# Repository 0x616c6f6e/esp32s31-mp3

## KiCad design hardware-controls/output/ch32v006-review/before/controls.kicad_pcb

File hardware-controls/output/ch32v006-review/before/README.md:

# 滑环与按键小板 B：I²C 四键＋独立 POWER

## 当前生产版本：2026-09-22，无测试点

已同步移除原理图和 PCB 中 TP1～TP11，清理 70 段分支走线及 5 个冗余过孔。当前为 31 个封装对象（26 个装配元件、1 个触摸电极、4 个安装孔）、442 段走线、52 个过孔。其余封装位置、接口针序和功能网络保持不变；ERC、DRC、未连接项和原理图一致性问题均为 0。

最新生产包：[controls-jlcpcb-20260922-no-tp-gerbers.zip](output/controls-jlcpcb-20260922-no-tp-gerbers.zip)。双层 FR-4、44 × 34 mm、0.8 mm 板厚，52 个 Ø0.30 mm 镀铜过孔、4 个 Ø1.80 mm 非金属化安装孔。请使用此包，旧带测试点版仅保留作历史记录。最新 BOM 为 [controls-jlcpcb-20260922-bom.csv](output/controls-jlcpcb-20260922-bom.csv)，10 类、单板 26 个元件，LCSC 料号尚待匹配。

检查报告、前后对比图及修改前备份位于 [output/remove-testpoints](output/remove-testpoints/README.md)。旧 STEP / FreeCAD 装配未重新导出。

## 2026-09-22 GND 铺铜优化

当前 `controls.kicad_pcb` 已增加双面 GND 铺铜，GND 走线从 99 段减至 75 段（减少约 26.59 mm），保留 12 个必要的 GND 过孔。E1 触摸电极及其背面设置禁铺铜区，轮廓外扩约 0.8 mm；三路 WHEEL/SENSE 走线按铜边再外扩约 0.5 mm 避让。这些是本版设计余量，触摸灵敏度仍需结合覆盖层实测调参。

铺铜间距 0.20 mm、最小铜宽 0.25 mm、热焊盘间隙/辐条宽 0.20 mm，移除孤立铜岛。所有封装定义、元件位置、原理图、信号走线和板框均保持不变。KiCad 10.0.4 原生重铺铜后的 DRC 为 0 违规、0 未连接、0 原理图一致性问题。

此次铺铜阶段报告、前后对比图及备份位于 [output/ground-plane-review](output/ground-plane-review/README.md)。对应的 `controls-jlcpcb-20260922-gerbers.zip` 带有测试点，已被上面的无测试点版替代。下文旧 `fabrication/`、Gerber ZIP 以及历史 STEP 和 validation/fit 报告均为历史版本。

打开 **controls.kicad_pro**。这是独立工程，已按用户完成布局的 `hardware-q2-layout` 主板设计 FFC 对接，主板文件未修改；原理图与 PCB 的符号路径和网络已对应。配套装配为 `mechanical/Q2_Controls_Assembly.FCStd`。

## 电路与布局

- 44 × 34 × 0.8 mm、R10、双层板；沿用 F 版外壳的四个 Ø1.8 安装孔和五个按键中心。
- 正面 E1 为三个相互插值的电容触摸电极，外径 31 mm、内径 15 mm，留出四个开关窗口。电极覆盖阻焊，无锡膏；不使用旧机械模型里的十二个示意扇区。
- U1：AT42QT2120-MMHR，3.3 V，I²C 地址 0x1C。三路 10 kΩ 采样串阻、22 Ω 电源滤波、100 nF / 1 µF 去耦；SDA/SCL 各 4.7 kΩ 上拉，共享 INT_N / RESET_N 各 10 kΩ 上拉。
- U2：TCA6408ARGTR，RGT VQFN-16，3 × 3 mm，0.5 mm 脚距，最大高 1 mm。ADDR 接地，7 位地址 0x20；VCCI、VCCP 共用 +3V3，各有 100 nF 去耦。散热焊盘接地。封装焊盘和本地包络模型依据 TI RGT0016A 图。
- 五个 ALPS SKSWCEE010，3 × 2 mm、标称高 0.6 ±0.05 mm、1.8 N、行程 0.13 mm。BACK / PREV / NEXT / PLAY 分别接 U2 P0 / P1 / P2 / P3，R9…R12 各 47 kΩ 上拉，按下为低；只通过 I²C 向外部主机报告这四键。
- POWER 独立引出：SW1.1 → J1.11，R14 = 10 kΩ 上拉至小板 +3V3；上电后松开为高、按下接地为低。不接 U1/U2，按下时上拉支路电流约 0.33 mA。高电平依赖小板供电，本版未实现整机开关机；若需要关机唤醒，须在主板设计中确认上拉电源为常供电域。
- U2 未用的 P4…P7 共接 UNUSED_INPUTS，由 R13 = 10 kΩ 下拉，避免上电浮空。这四脚必须一直配置为输入；不要用作输出或连接外设。
- U1 CHANGE 和 U2 INT 均为开漏输出，共接 INT_N；RESET_N 也由两芯片共用。主控轮询仅需 SDA/SCL，有中断通知时合计 3 个 IO；RESET_N 是可选调试/恢复信号，不接时由上拉保持高。
- 芯片及无源件在背面、避开电池和马达占位。新增 U2 与无源件布置在电池下方区域，正面五键及板框不变。J1 改为与主板 FPC1 相同的 HC-FPC-05-10-12RLTAG，12 芯、0.5 mm 间距、下接点，适配 0.30 ±0.03 mm 端部厚度。KiCad 坐标 (8.130, 9.411) mm、B.Cu、−90°；它不是屏幕接口。
- 已完成新主板 FPC1 与小板 J1 的针序对照和 40 mm 成品 FFC 名义装配路线；详见 [FFC 对接与采购说明](mechanical/FFC-INTERCONNECT.md)。整机开关机逻辑与实物连接尚未验证。

## J1 引脚

按 **焊盘编号** 接线，不能根据排线同面／反面的外观直接推断另一端编号。

| 引脚 | 信号 | 用途 |
|---|---|---|
| 1 | GND | 地 |
| 2 | +3V3 | 稳压 3.3 V 输入 |
| 3 | SDA | I²C 数据 |
| 4 | SCL | I²C 时钟 |
| 5 | INT_N | 滑环＋四键共享低有效开漏中断 |
| 6 | RESET_N | 两芯片共享低有效复位；可不接 |
| 7…10 | NC | 不连接；不再引出四个普通按键 |
| 11 | KEY_POWER | 独立电源键，10 kΩ 上拉；按下为低 |
| 12 | GND | 地 |
| 13、14 | GND | 金属固定脚，不计入 12 芯排线 |

TP1～TP11 已移除。调试电源、I²C、中断、复位和 POWER 可从 J1 对应引脚测量，四个机械键输入可从 U2 或开关焊盘测量。

## 独立上电与调试

1. 用限流的稳压 3.3 V 给 J1.2/J1.1 供电。不得输入电池原始电压。主机逻辑电平也使用 3.3 V。
2. 先以 100 kHz I²C 访问 7 位地址 0x1C，读寄存器 0x00，预期芯片 ID 为 0x3E。
3. 寄存器 0x0E 写 0xC0，启用 KEY0…KEY2 的环形模式；KEY0…KEY2 的控制寄存器保持触摸输入配置。
4. 未使用的 KEY3…KEY11 不应浮空扫描：对应十进制地址 31…39 的控制寄存器写 0x01，配置为输出低电平，焊盘不接外部网络。配置后按数据手册执行重新校准，并等待校准完成。
5. 读取检测状态和滑环位置，检查一整圈的连续性、零点回绕、方向及按压时的误触。阈值、脉冲数、积分、低功耗周期须结合成品覆盖层实测设定；本项目没有凭空填入“已验证”的灵敏度参数。
6. 初始化 U2，访问 7 位地址 0x20：先向输出寄存器 0x01 写 0x00（设安全的输出锁存值，不改变方向），向极性寄存器 0x02 写 0x00，向方向寄存器 0x03 写 0xFF，保持所有端口为输入。读回 0x02 / 0x03 核对配置。不要把共接的 P4…P7 配成输出。
7. 读取 U2 输入寄存器 0x00。正常未按时低四位为 0x0F，高四位为 0；`pressed = (~input) & 0x0F`。bit0=BACK，bit1=PREV，bit2=NEXT，bit3=PLAY，可识别同时按下。建议每 5 ms 采样并连续稳定 20 ms 后确认变化；长按/连击由主控处理。
8. INT_N 触发时，分别读取 U1 的状态字节和 U2 的输入寄存器，清除两边的中断来源；只读取其中一颗可能让中断一直为低。初始化后主动读一次两颗芯片，正常服务中应持续处理到 INT_N 释放，并设置有界重试、周期补读及总线错误恢复，不能仅等待下一个下降沿。即使中断已释放，也继续定时采样直到机械键消抖完成；U2 不会为静止的按键反复触发中断。
9. 小板上电后测试 POWER：J1.11 松开时约 3.3 V，按下时约 0 V；确认不影响 U2 低四位。R14 已提供上拉，主机端按 3.3 V 逻辑输入读取并进行消抖。未来接入整机电源管理时确认其电源域和关机唤醒要求。

若测试主机已有 I²C 上拉，应计算并联后的总阻值，必要时不装 R4/R5。RESET_N 未连接时由 R7 保持高电平；外部拉低至少 10 ms 并释放后须重新初始化两颗 IC，等待触摸校准完成。J1 输入电源应与主机 I²C 电平同步，不能在小板断电时持续用信号线反向供电。小板掉电重启后也必须重新初始化。

## 外壳适配

`mechanical/` 单独保存适配版本，没有覆盖 F 版外壳源文件。

- 保持整机外观、按键中心、板框和安装高度。小板下表面 Z=11.1、上表面 Z=11.9 mm。
- 修正原键帽的内部压柱、限位环和壳体内部环槽；旧键帽直接套用会在开关触发前碰到 PCB。
- 新压柱底面 Z=12.65 mm。考虑开关高度公差，静态间隙为 0.10…0.20 mm；名义触发行程 0.28 mm，按高度下限计算为 0.33 mm。
- `fit-check.json` 检查小板和 26 个元件、电池／移位后的马达／新主板已建模元件与外壳的名义实体相交（不包含未重布的电池和马达线束），检查 0.33 mm 轴向下压，以及四个方向的约 ±0.727° 倾斜加 0.165 mm 下移姿态。U2 包络使用最大 1 mm 高度；其他尺寸仍为名义尺寸。这些姿态只证明有可用运动空间，不等同于受力、回弹、摇摆手感或寿命验证，需打印实物确认。
- 电池仍为 24 × 34 × 3 mm 占位，板底到电池名义间隙仅 0.3 mm；实际电池厚度、膨胀余量及绝缘层需要重新核对，不能据此选用更厚电池。
- 滑环上方存在约 1.05 mm 空气间隙及 0.6 mm 键帽。键帽使用非导电塑料，不做导电镀层。空气间隙与按压运动会影响触摸，需要整机调试；本版是待验证的原型设计。

FreeCAD 文件包含可重算的内部圆柱、切除与融合特征；`HousingControlsA`、`WheelControlsA`、`CenterButtonControlsA` 分别提供 STEP / STL，后盖增加局部内部 FFC 避让槽并导出 `RearCoverWithPCBPosts.step/.stl`，外表面保持不变。马达中心从壳体 (39, 57) 移到 (39, 62) mm，电池不变；U1 向壳体 +X 平移 0.6 mm 以避让新主板耳机座。新主板 1.6 mm 厚；2026-09-22 完整复查确认最终主板四个安装孔与原固定柱对齐；同时发现马达/耳机座及 C13/屏幕排线干涉，不能将旧的局部通过报告视为整机装配通过。最新装配与报告见 `../mechanical/final-board-review/`。打开装配默认显示外观，可展开 `ControlsPCB`、`References` 查看内部。

## 文件与检查

- `controls.kicad_sch` / `controls.kicad_pcb`：实际独立小板设计；本地 `Controls.pretty`、`Controls.kicad_sym`、`models3d` 随工程携带。
- `output/bom.csv`：26 个装配元件的型号与数据手册。
- `output/erc.json`、`output/drc.json`、`output/validation.json`：最终原生 KiCad 检查与保存文件的校验摘要。
- `fabrication/`：双面 Gerber、钢网层及分开的 PTH / NPTH 钻孔；`output/controls-B-prototype-gerbers.zip` 为 B 版原型打样包。制造参数见包内说明。
- `output/schematic.png` / `output/schematic/controls.svg`：可直接查看的原理图。
- `output/controls-populated.step`：小板 STEP；FreeCAD 检查将 KiCad 导出的介质厚度扩展为 0.8 mm 成品板包络。
- `mechanical/fit-check.json`：名义装配与轴向行程检查，包含源文件校验值。

本版尚未经过实物焊接、触摸调参、ESD、按键寿命或整机验证。DRC/ERC 与名义几何通过只证明相应的设计规则和包络检查通过。

## 设计依据与重建

原厂资料保存在 `reference/`，来源：[Microchip AT42QT2120](https://ww1.microchip.com/downloads/en/devicedoc/doc9634.pdf)、[Microchip QTAN0079](https://ww1.microchip.com/downloads/aemDocuments/documents/OTH/ApplicationNotes/ApplicationNotes/doc10752.pdf)、[ALPS SKSW](https://tech.alpsalpine.com/cms.media/product_catalog_ta_02_sksw_en_ee3e98d509.pdf)、[Hirose FH19C](https://www.hirose.com/en/product/p/CL0580-0413-0-10)。电极窗口和形状是本项目的实现，并非厂家验证过的参考 PCB。

B 版新增 [TI TCA6408A 数据手册](https://www.ti.com/lit/ds/symlink/tca6408a.pdf)：§5 核对 RGT 引脚；§8.3.3 开漏中断；§8.6 寄存器/0x20 地址；RGT0016A 图核对 3 × 3 mm / EP 1.45 × 1.45 mm 封装。A 版机械零件内部名称 `HousingControlsA` 等保留，保留历史名称；本次新增后盖内部排线避让，不改变外观和按键中心。

`make_electrodes.py` 需要 Python + Shapely；`build_design.py`、`finalize_board.py`、`validate.py` 使用 KiCad 10 的 Python/pcbnew；`build_models.py`、`build_fit.py` 使用 FreeCAD 1.1。生成脚本是本版设计记录，不应在手工修改后直接重跑覆盖。`build_design.py` 只生成初始原理图和摆放，会拒绝覆盖已有走线的板，不会重建最终布线。最终布线直接保存在 PCB；对应交换记录及说明在 `reference/routing/`。原生 KiCad DRC、连通性和原理图一致性是交付检查依据。

本次连接器依据 [HCTL HC-FPC-05-10 原厂图纸](https://atta.szlcsc.com/upload/public/pdf/source/20221027/B2DE489DA152049D1F105170189CFB4E.pdf)，本地副本为 `reference/HCTL-HC-FPC-05-10.pdf`。旧 Hirose 资料仅保留为历史参考，不能按其 0.2 mm 排线规格采购新 J1 的排线。

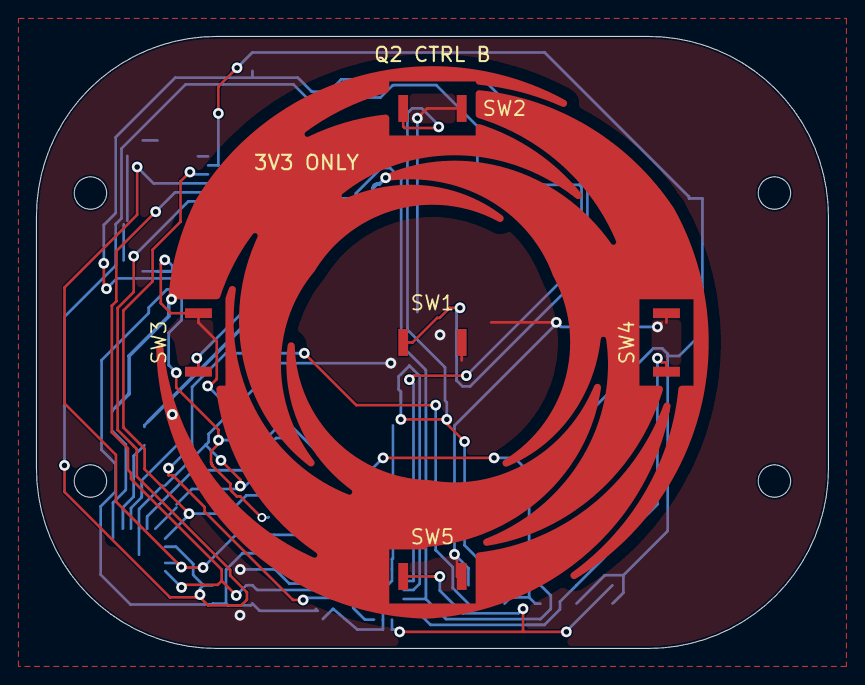
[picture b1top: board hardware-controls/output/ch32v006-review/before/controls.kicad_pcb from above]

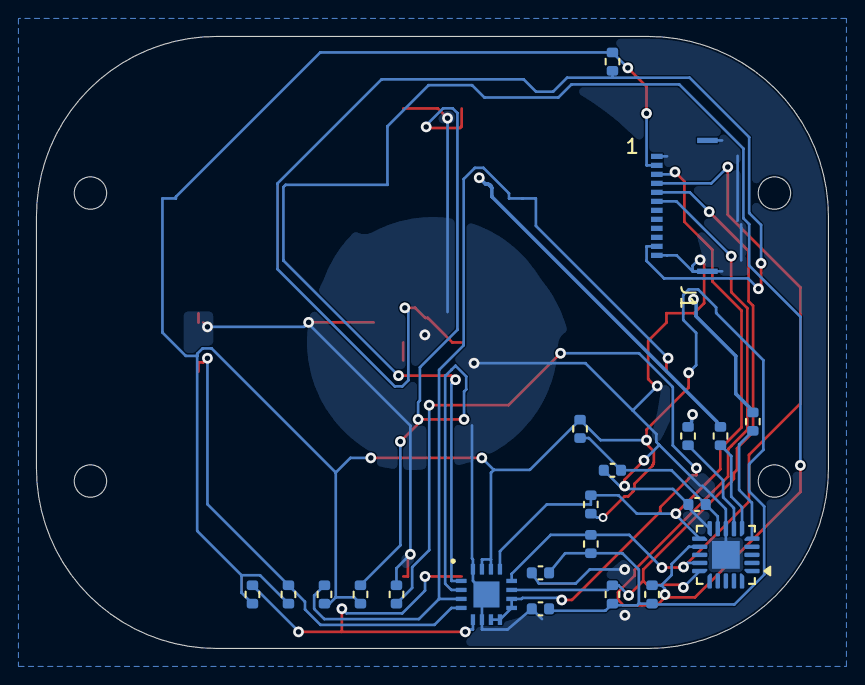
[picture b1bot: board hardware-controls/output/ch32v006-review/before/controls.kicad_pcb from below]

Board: 2 copper layers, 44.0 x 34.0 mm, 31 parts (21 on the bottom side), 19 nets.

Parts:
C1, C3, C4: 100nF; C0402
C2: 1uF; C0402
E1: 31mm INTERPOLATED WHEEL; Wheel_D31
H1, H2, H3, H4: M1.6 / NPTH 1.8; Mount_1.8
J1: HC-FPC-05-10-12RLTAG; HCTL_FPC12
R1, R2, R3, R6, R7, R13, R14: 10k; R0402
R4, R5: 4.7k; R0402
R8: 22R; R0402
R9, R10, R11, R12: 47k; R0402
SW1, SW2, SW3, SW4, SW5: SKSWCEE010; SKSW_3x2
U1: AT42QT2120-MMHR; QT2120_VQFN20
U2: TCA6408ARGTR; TCA6408A_VQFN16

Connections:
/+3V3: C3.1, C4.1, J1.2, R4.1, R5.1, R6.1, R7.1, R8.1, R9.1, R10.1, R11.1, R12.1, R14.1, U2.14, U2.15
/GND: C1.2, C2.2, C3.2, C4.2, J1.1, J1.12, J1.13, J1.14, R13.2, SW1.2, SW2.2, SW3.2, SW4.2, SW5.2, U1.8, U1.10, U1.21, U2.6, U2.16, U2.17
/INT_N: J1.5, R6.2, U1.15, U2.11
/KEY_BACK: R9.2, SW2.1, U2.2
/KEY_NEXT: R11.2, SW4.1, U2.4
/KEY_PLAY: R12.2, SW5.1, U2.5
/KEY_POWER: J1.11, R14.2, SW1.1
/KEY_PREV: R10.2, SW3.1, U2.3
/RESET_N: J1.6, R7.2, U1.12, U2.1
/SCL: J1.4, R5.2, U1.14, U2.12
/SDA: J1.3, R4.2, U1.11, U2.13
/SENSE0: R1.2, U1.7
/SENSE1: R2.2, U1.6
/SENSE2: R3.2, U1.5
/UNUSED_INPUTS: R13.1, U2.7, U2.8, U2.9, U2.10
/VDD_TOUCH: C1.1, C2.1, R8.2, U1.9
/WHEEL0: E1.1, R1.1
/WHEEL1: E1.2, R2.1
/WHEEL2: E1.3, R3.1

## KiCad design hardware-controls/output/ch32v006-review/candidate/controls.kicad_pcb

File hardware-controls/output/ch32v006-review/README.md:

# CH32V006 C 版迁移检查

源电路为 AT42QT2120 + TCA6408A；目标为单颗 CH32V006F8U6。`before/` 是本次操作前的原文件备份；`candidate/` 是工作候选文件。以 hardware-controls 根目录中的最终工程为准，不要从这里的中间 PCB 导出生产文件。

`design.json` 记录本版原理图 UUID、元件、实际 KiCad 顶视坐标、MCU 引脚与 FPC 接口。这里的坐标是实际 PCB 坐标，不能直接交给历史脚本中采用 `44-x` 镜像约定的机械生成器。

检查报告以 `final-erc.json`、`final-drc.json`、`validation.json` 为准；带 pre-route / routed / fanout / grid 字样的文件仅用于迁移过程诊断。模型预览用于检查元件体积与布局，不代替整机 FreeCAD 装配的干涉验证。

C 版需要新固件，详见 `../../CH32V006-interface.md`。本次没有生成可直接烧录的固件；旧 AT42 版本的 Gerber 和 BOM 不适用于 C 版。后续已于 2026-09-22 导出新版生产包 `../controls-ch32v006-jlcpcb-20260922-gerbers.zip`，导出检查记录见 `../ch32v006-gerber-review/manifest.json`。

最终检查：KiCad 10.0.4 ERC、DRC、未连接项、原理图一致性问题均为 0。新版 BOM 为 `../controls-ch32v006-bom.csv`，装配 STEP 为 `../controls-ch32v006.step`。J1、E1、SW1～SW5、H1～H4 和板框通过前后几何一致性检查。不要将这些电气与几何检查解释为固件或整机实测通过。

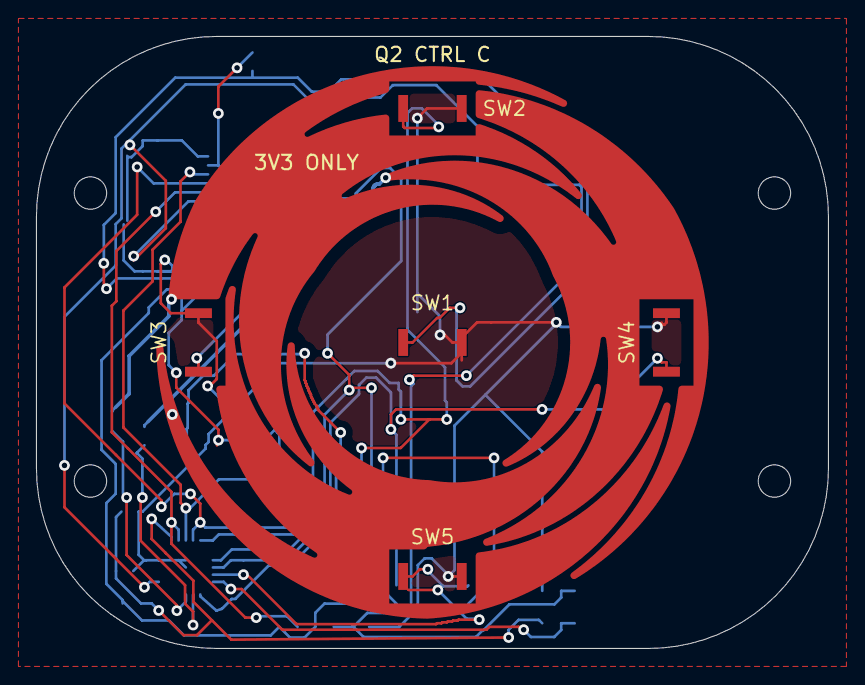
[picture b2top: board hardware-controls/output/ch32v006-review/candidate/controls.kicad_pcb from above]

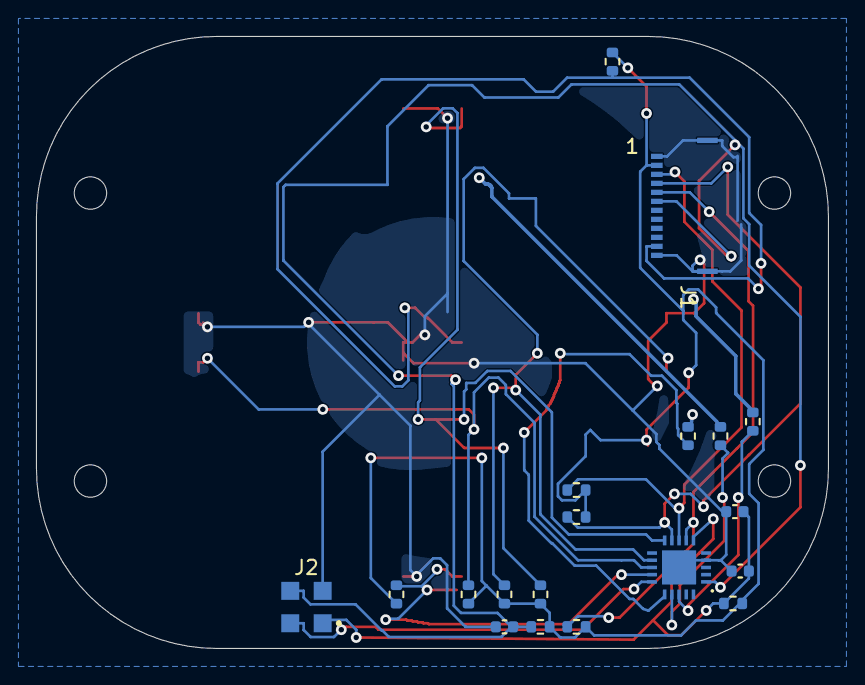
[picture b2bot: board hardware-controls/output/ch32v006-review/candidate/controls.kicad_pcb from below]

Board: 2 copper layers, 44.0 x 34.0 mm, 29 parts (19 on the bottom side), 19 nets.

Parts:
C1, C3: 100nF; C0402
C2: 1uF; C0402
E1: 31mm INTERPOLATED WHEEL; Wheel_D31
H1, H2, H3, H4: M1.6 / NPTH 1.8; Mount_1.8
J1: HC-FPC-05-10-12RLTAG; HCTL_FPC12
J2: WCH_SDI_PADS; SDI_4_Pads
R1, R2, R3: 1k; R0402
R4, R5: 4.7k; R0402
R6, R7, R14: 10k; R0402
R8: 0R; R0402
R9, R10, R11, R12: 47k; R0402
SW1, SW2, SW3, SW4, SW5: SKSWCEE010; SKSW_3x2
U1: CH32V006F8U6; CH32V006_QFN20

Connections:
/+3V3: J1.2, R4.1, R5.1, R6.1, R7.1, R8.1, R9.1, R10.1, R11.1, R12.1, R14.1
/GND: C1.2, C2.2, C3.2, J1.1, J1.12, J1.13 (SHIELD), J1.14 (SHIELD), J2.3 (GND), SW1.2, SW2.2, SW3.2, SW4.2, SW5.2, U1.0 (VSS_EP), U1.4 (VSS)
/INT_N: J1.5, R6.2, U1.7 (PC0/INT)
/KEY_BACK: R9.2, SW2.1, U1.10 (PC3)
/KEY_NEXT: R11.2, SW4.1, U1.13 (PC6)
/KEY_PLAY: R12.2, SW5.1, U1.14 (PC7)
/KEY_POWER: J1.11, R14.2, SW1.1
/KEY_PREV: R10.2, SW3.1, U1.12 (PC5)
/RESET_N: C3.1, J1.6, J2.4 (RESET_N), R7.2, U1.1 (PD7/~RST)
/SCL: J1.4, R5.2, U1.9 (PC2/SCL)
/SDA: J1.3, R4.2, U1.8 (PC1/SDA)
/SENSE0: R1.2, U1.16 (PD2/TKEY3)
/SENSE1: R2.2, U1.17 (PD3/TKEY4)
/SENSE2: R3.2, U1.18 (PD4/TKEY7)
/SWIO: J2.2 (SWIO), U1.15 (PD1/SWIO)
/VDD_MCU: C1.1, C2.1, J2.1 (VREF_3V3), R8.2, U1.6 (VDD)
/WHEEL0: E1.1 (CH0), R1.1
/WHEEL1: E1.2 (CH1), R2.1
/WHEEL2: E1.3 (CH2), R3.1
